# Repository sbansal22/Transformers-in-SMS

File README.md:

# Transformers-in-SMS
Transformers in SMS (CC1310-01) Olin 2020-2021 Co-Curricular

#### Schematic

#### Routing

#### Layout

## Ordering PCBs From JLCPCB

For ordering the boards, go to JLCPCB.com (https://jlcpcb.com/RAT), and click on "Quote Now" button.

JLCPCB (ShenzhenJLC Electronics Co., Ltd.), is the largest PCB prototype enterprise in China, and a high-tech manufacturer specializing in quick PCB prototype and small-batch PCB production. You can order a minimum of 5 PCBs for just $2.

First: Upload the gerber files for the board by clicking the "Add gerber file" button. You’ll notice a message at the bottom if the file is successfully uploaded.

A correctly uploaded gerber folder renders the board as follows:

Second: In order to get the board assembled (optional, based on the project requirements), select the "SMT Assembly option. It is important to select the side of the PCB that needs to be assembled, as well as the quantity for SMT. Press the "Confirm" button, then press the "Next" button.

Third: upload the BOM (Bill of Material) and CPL (Component Placement List) files and click the "Next" button. It is necessary to make sure that each of these files follow the jlcpcb specified BOM and CPL formats, respectively:

- [Sample BOM](https://jlcpcb.com//video/JLCSMT_Sample_BOM1.xlsx?_ga=2.42560357.1905056644.1612161700-100444678.1610257845)
- [Sample CPL](https://jlcpcb.com//video/JLCSMT_Sample_CPL1.xlsx?_ga=2.42560357.1905056644.1612161700-100444678.1610257845)
- [SMT FAQ's](https://support.jlcpcb.com/category/78-smt-assembly?_ga=2.42560357.1905056644.1612161700-100444678.1610257845)

Note: If there is an issue with the BOM/CPL formatting, the the page will keep erroring out until it is resolved.

Fourth: The parts are automatically detected through the uploaded BOM. They are also matched against jlcpcb's in-stock parts. It is important to go through each row and confirm if the auto-detected parts are the desired parts. Some parts will remain undetected if they cannot be assembled through SMT and require manual assembly post-deilvery.

Fifth: The website renders an assembled board using the CPL file. This feature can be used to review the placement of the components (including orientation). Once carefull reviewed, the next step is to download a list of parts remaining to be assembled towards the bottom of this page view. It is important to place an order for the remaining components to be manually assembled upon delivery.

Sixth: Click on the “Save to Cart” button. Then, click on the "Secure Checkout" button.

Last: Add the payment details and choose the suitable delivery method (this includes FedEx, DHL, and standard mail options). Then, place the order.

Optional: To review the production status of the board, click on the "Order History" button under username. Then, click on In Production > view progress to obtain timestamps for each of the production steps in real time.

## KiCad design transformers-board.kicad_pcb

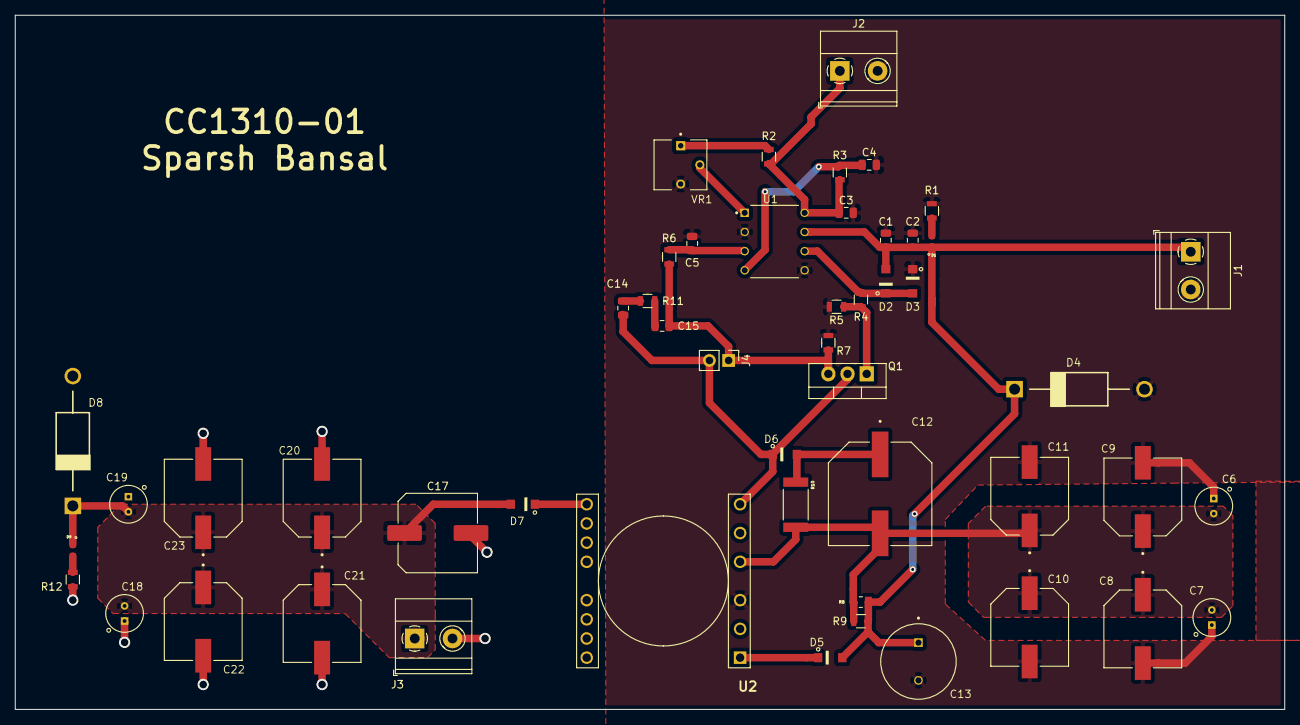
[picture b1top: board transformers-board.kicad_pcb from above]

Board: 2 copper layers, 168.1 x 91.9 mm, 51 parts (0 on the bottom side), 21 nets.

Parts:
C1, C2, C3: GRM21BR71H104KA01L; C_0805_2012Metric
C4: 1000pF; C_0805_2012Metric
C5: 100pF; C_0805_2012Metric
C6, C7, C18, C19: ECA1HM100; CAPPRD200W50D500H1100B
C8, C9, C10, C11, C20, C21, C22, C23: EEHZA1H101P; CAPAE1030X1050N
C12: 200uF; CAPAE1350X1400N
C13: 120uF; CAPPRD500W60D1000H1800
C14: 1.014nF; C_0805_2012Metric
C15: 08051A471JAT2A; C_0805_2012Metric
C17: EGPA500ELL222ML40S; C_Elec_10x10.2
D1, D9: LTST-C190GKT; LEDM1608X80
D2, D3, D5, D6, D7: SS2FL4-M3/H; SODFL3718X108N
D4, D8: 1N5357BRLG; DIOAD1720W120L750D440P
J1, J2, J3: Screw_Terminal_01x02; TerminalBlock_Phoenix_MKDS-1,5-2_1x02_P5.00mm_Horizontal
J4: Conn_01x02_Male; PinHeader_1x02_P2.54mm_Vertical
Q1: IRF3205; TO-220-3_Vertical
R1: 100; R_0805_OEM
R2: R_100; R_0805_OEM
R3: R_4.7K; R_0805_OEM
R4: 10; R_0805_OEM
R5, R6: 10K; R_0805_OEM
R7: 0.05; R_0805_OEM
R8: CRCW08050000Z0EA
R9: R_100K; R_0805_OEM
R10: CRCW251210K7FKEG
R11: 15; R_0805_OEM
R12: R_10K; R_0805_OEM
U1: UC2844NG4; DIP794W45P254L959H508Q8
U2: PC47PQ20_16Z-22; CPVPQ20161S14PZ
VR1: 3362P-1-102LF; TRIM_3362P-1-102LF

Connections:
+5V: C3.1, J2.1, R2.1, R3.1, U1.8
GND: C1.2, C2.2, C3.2, C4.2, C5.2, C6.2, C7.2, C8.2, C9.2, C10.2, C11.2, C13.2, D3.2, D4.2, J1.2, J2.2, R1.2, R5.1, R7.1, U1.2, U1.5, U2.3, VR1.3
GNDA: C17.2, C18.2, C19.2, C20.2, C21.2, C22.2, C23.2, D8.2, J3.2, R12.2, U2.10
unnamed: C4.1, R3.2, U1.4
unnamed: C5.1, R6.1, U1.3
unnamed: C6.1, C7.1, C8.1, C9.1, C10.1, C11.1, C12.2, R8.1, R9.1, R10.2, U2.4
unnamed: C12.1, D6.1, R10.1
unnamed: C14.1, D6.2, J4.2, Q1.2, U2.6
unnamed: C14.2, R11.2
unnamed: C15.1, R11.1
unnamed: C15.2, J4.1, Q1.3, R6.2, R7.2
unnamed: D1.1, R1.1
unnamed: D2.2, D3.1, R4.1, U1.6
unnamed: D5.2, U2.1
unnamed: D7.2, U2.7
unnamed: D9.1, R12.1
unnamed: Q1.1, R4.2, R5.2
unnamed: R2.2, VR1.1
unnamed: U1.1, VR1.2
VCC: C1.1, C2.1, C13.1, D1.2, D2.1, D4.1, D5.1, J1.1, R8.2, R9.2, U1.7
VCCQ: C17.1, C18.1, C19.1, C20.1, C21.1, C22.1, C23.1, D7.1, D8.1, D9.2, J3.1

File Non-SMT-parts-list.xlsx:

Designator | Comment | Footprint | Quantity
D2,D3,D5,D6,D7 | SS2FL4-M3/H | SODFL3718X108N | 5.0
R10 | CRCW251210K7FKEG | CRCW251210K7FKEG | 1.0
C8,C9,C10,C11,C20,C21,C22,C23 | EEHZA1H101P | CAPAE1030X1050N | 8.0
C1,C2,C3 | GRM21BR71H104KA01L | 0805_C | 3.0
U2 | PC47PQ20_16Z-22 | CPVPQ20161S14PZ | 0.0
J4 | CONN_01X02_MALE | PINHEADER_1X02_P2.54MM_VERTICAL | 0.0
Q1 | IRF3205 | TO-220-3_VERTICAL | 0.0
C6,C7,C18,C19 | ECA1HM100 | CAPPRD200W50D500H1100B | 0.0
C13 | 120UF | CAPPRD500W60D1000H1800 | 0.0
U1 | UC2844NG4 | DIP794W45P254L959H508Q8 | 0.0
D4,D8 | 1N5357BRLG | DIOAD1720W120L750D440P | 0.0
DESIGNATOR | COMMENT | FOOTPRINT | 0.0
J1,J2,J3 | SCREW_TERMINAL_01X02 | TERMINALBLOCK_PHOENIX_MKDS-1,5-2_1X02_P5.00MM_HORIZONTAL | 0.0
VR1 | 3362P-1-102LF | TRIM_3362P-1-102LF | 0.0

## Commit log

2021-04-03 Add initial KiCAD board files
2021-04-03 Add renders
2021-04-04 Add layout updates
2021-04-09 Make changes for Beat's comments
2021-04-19 Add fabrication outputs
2021-04-19 Add gerbers
2021-04-19 Add fabrication outputs (for real this time)
2021-04-25 Add ordering information
